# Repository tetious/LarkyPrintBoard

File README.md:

# LarkyPrintBoard
This is the PCB for the Lark printer board!

The Lark sits between your printer and it's RAMPSish LCD/SD card board and provides a fast and easy to use web 
interface for printing from SD cards. 

It "just works" with most printers/firmwares that support the "LCD Smart Display" style 2-line text LCD.

With minor tweaks, it should work with any printer that supports Marlin.

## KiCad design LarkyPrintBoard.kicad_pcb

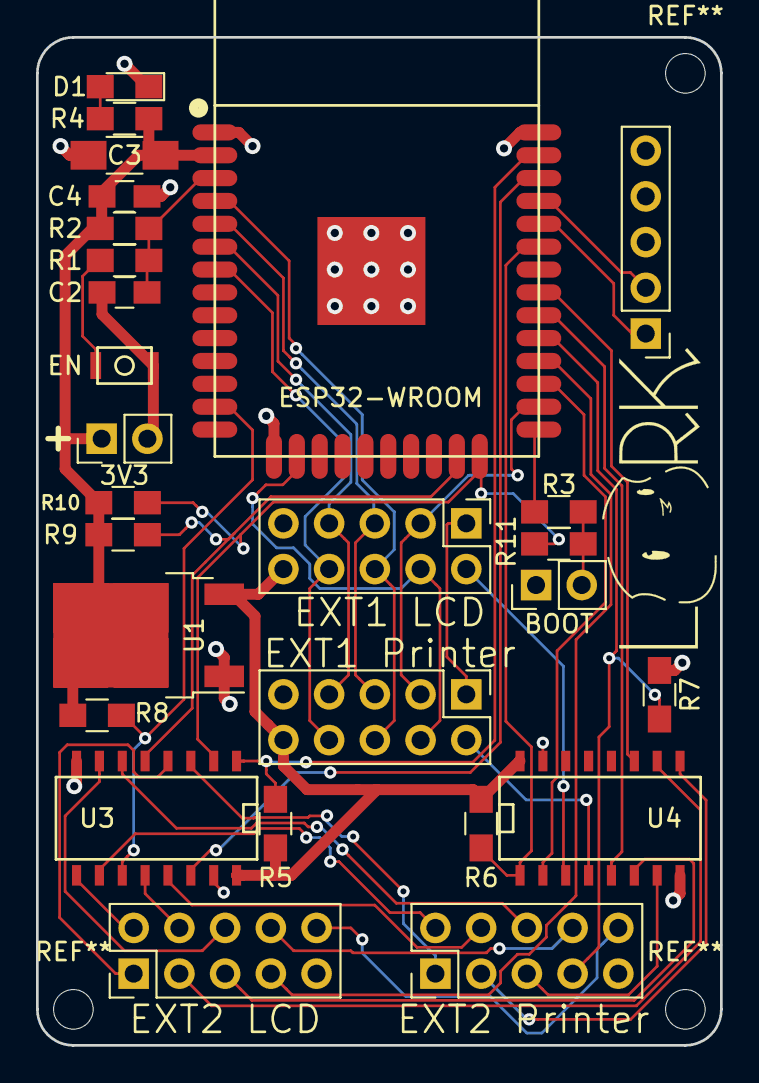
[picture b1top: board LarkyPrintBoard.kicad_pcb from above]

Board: 2 copper layers, 38.0 x 56.0 mm, 27 parts (0 on the bottom side), 44 nets.

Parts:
C2: 1nf; C_0805_HandSoldering
C3: 100uF; C_1206_HandSoldering
C4: 1uf; C_0805_HandSoldering
D1: LED; LED_0805_HandSoldering
J1: EXT1 Printer; Pin_Header_Straight_2x05_Pitch2.54mm
J2: EXT2 LCD; Pin_Header_Straight_2x05_Pitch2.54mm
J3: EXT1 LCD; Pin_Header_Straight_2x05_Pitch2.54mm
J4: EXT2 Printer; Pin_Header_Straight_2x05_Pitch2.54mm
J5: UART; Pin_Header_Straight_1x05_Pitch2.54mm
J6: EN; KXT131LHS
J7: BOOT; Pin_Header_Straight_1x02_Pitch2.54mm
J8: 3V3; Pin_Header_Straight_1x02_Pitch2.54mm
R1, R3, R4, R11: 680; R_0805_HandSoldering
R2, R5, R6, R7, R8, R9, R10: 10K; R_0805_HandSoldering
U1: LM1117-3.3; TO-252-2
U2: ESP32-WROOM
U3, U4: CBT3257A; SO-16-N

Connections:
+3V3: C3.2, C4.2, J8.1, R2.1, R4.2, R8.1, R9.1, R10.1, U1.2, U2.2
+5V: J1.10, J3.10, R5.2, R6.2, U1.3, U3.16, U4.16
/BEEP: J1.1, J3.1
/BOOT: R3.1, U2.25
/EN: C2.1, R1.1, R2.2, U2.3
/ENC_1_I: J2.5, U4.6
/ENC_1_O: J4.5, U4.7
/ENC_2_I: J2.3, U4.10
/ENC_2_O: J4.3, U4.9
/ENC_BTN_I: J1.2, U4.4
/ENC_BTN_O: J3.2, U4.3
/ENC_MUX_S: R6.1, U2.33, U4.1
/ESP_ENC_1: U2.30, U4.5
/ESP_ENC_2: U2.31, U4.11
/ESP_ENC_BTN: U2.27, U4.2
/ESP_RX: J5.1, U2.34
/ESP_SD_SS: U2.36, U3.14
/ESP_SPI_MISO: R10.2, R11.1, U2.24, U3.2
/ESP_SPI_MOSI: R9.2, U2.23, U3.5
/ESP_SPI_SCK: R8.2, U2.13, U3.11
/ESP_TX: J5.2, U2.35
/KILL: J2.10, J4.10
/LCD4: J1.5, J3.5, U2.5
/LCD5: J1.6, J3.6, U2.4
/LCD6: J1.7, J3.7, U2.6
/LCD7: J1.8, J3.8, U2.7
/LCD_EN: J1.3, J3.3, U2.26
/LCD_RS: J1.4, J3.4, U2.16
/RESET: J2.8, J4.8
/SD_DETECT_I: J2.7, U2.28
/SD_DETECT_O: J4.7, R7.2, U2.29
/SD_MISO_I: J2.1, U3.4
/SD_MISO_O: J4.1, U3.3
/SD_MOSI_I: J2.6, U3.7
/SD_MOSI_O: J4.6, U3.6
/SD_MUX_S: R5.1, U2.37, U3.1
/SD_SCK_I: J2.2, U3.9
/SD_SCK_O: J4.2, U3.10
/SD_SS_I: J2.4, U3.12
/SD_SS_O: J4.4, U3.13
GND: C2.2, C3.1, C4.1, D1.1, J1.9, J2.9, J3.9, J4.9, J5.5, J6.2, J7.1, J8.2, R7.1, U1.1, U2.1, U2.15, U2.38, U2.39, U3.8, U3.15, U4.8, U4.15
unnamed: D1.2, R4.1
unnamed: J6.1, R1.2
unnamed: J7.2, R3.2, R11.2

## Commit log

2017-09-05 Initial checkin.
2017-09-07 Fix output pins on input only ESP32 pins. Add JTAG. Tweaks and improvements.
2017-09-07 Alpha 1 final.
2017-09-07 Minor tweaks to document settings.
2017-09-24 Tons of changes and fixes. R1A2
2017-09-25 Minor tweaks.
2019-07-30 Create LICENSE
2020-05-09 Update something. ;)

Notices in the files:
LarkyPrintBoard.kicad_pcb:
Copyright Greg Lincoln
CC BY-NC-SA
